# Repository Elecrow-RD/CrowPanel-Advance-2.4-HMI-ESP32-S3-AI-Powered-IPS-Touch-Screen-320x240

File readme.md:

## Menu
### 1, Product picture
### 2, Product version number
### 3, product information
### 4, Use the driver module
### 5,Quick Start
### 6,Folder structure.
### 7,Pin definition
### 8,Guidelines for downloading some of the files from the github repository

### 1, Product picture

### 2, Product version number

|      | Hardware | Software | Remark |
| ---- | -------- | -------- | ------ |
| 1    | V1.0     | V1.0     | old |
| 1    | V1.1     | V1.1     | old |
| 1    | V1.2     | V1.2     | latest |

### Version update points:

**Version 1.1** 

V1.1 upgraded, optimized the amplifier circuit, better sound quality, and use IO21 to control mute. i2s_mic changed to two pins IO9 and IO10 control.

**Version 1.2** 

Only the button component has been updated. All other hardware and I/O pins remain the same as in the previous version.

### 3, product information

| Main Chip-**ESP32-S3-WROOM-1-N16R8**         |                                                              |
| -------------------------------------------- | ------------------------------------------------------------ |
| CPU/SoC                                      | high-performance Xtensa 32-bit LX7 dual-core processor, with a  up to 240MHz |
| System Memory                                | 512KB SRAM、8M PSRAM                                         |
| Memory                                       | 16M Flash，384KB ROM                                         |
| Development Language                         | MicroPython、C/C++                                           |
| Development Environment                      | ESP-IDF、Arduino IDE、LVGL、PlatformIO、MicroPython         |
| **Screen**                                   |                                                              |
| Size                                         | 2.4 inch                                                     |
| Diver IC                                     | ST7789                                                       |
| Resolution                                   | 800*480                                                      |
| Display Panel                                | IPS Panel                                                    |
| Touch Panel                                  | Capacitive Single Touch                                      |
| Viewing Angle                                | 178°                                                         |
| Brightness                                   | 400 cd/m²(Typ.)                                              |
| Color Depth                                  | 16-bit                                                       |
| **Wireless Communication - Onboard Antenna** |                                                              |
| WiFi                                         | Support 2.4GHz, 802.11a/b/g/n                                |
| Bluetooth                                    | Support Bluetooth 5.0 and BLE                                |
| Other                                        | **Zigbee、nRF2401、Matter、Thread and Wi-Fi 6 (Optional)**   |
| **Interface/Function**                       |                                                              |
| Interface                                    | USB port, UART, I2C, SD card slot, battery socket, speaker port, microphone, etc. |
| Function                                     | Audio amplifier, volume control, battery charge management, USB to UART, etc. |
| **Button/LED Indicator**                     |                                                              |
| Reset Button                                 | Yes, press to reset device                                   |
| Boot Button                                  | Yes, press and hold the power button to burn the program     |
| PWR                                          | Power indicator                                              |
| CHG                                          | Lithium battery charging status, completion indication       |
| **Other**                                    |                                                              |
| Installation method                          | Back hanging, fixed hole                                     |
| Operating temperature                        | -20~70 °C                                                    |
| Storage temperature                          | -30~80 °C                                                    |
| Power Input                                  | 5V/2A, USB or UART terminal                                  |
| Dimensions                                   | 77.1*51.8*15.8*mm                                            |

### 4, Use the driver module

| Name   | dependency library                      |
| ------ | --------------------------------------- |
| LVGL   | lvgl/lvgl@8.3.3                         |
| ST7789 | Adafruit GFX Library<br/>version=1.11.0 |

### 5,Quick Start

### Arduino IDE starts

#### Teaching Case Path：./example/example_code2.4

1.Download the library files used by this product to the 'libraries' folder.

C:\Users\Documents\Arduino\libraries\

2.Open the Arduino IDE

3.Open the code configuration environment and burn it

### ESP-IDF starts

#### Teaching Case Path：./example/idf_code

1.Right-click on an empty space in the project folder and select "Open with VS Code" to open the project.

2.In the IDF plug-in, select the port, then compile and flash

### 6,Folder structure.

|--3D file： Contains 3D model files (.stp) for the hardware. These files can be used for visualization, enclosure design, or integration into CAD software.

|--Datasheet: Includes datasheets for components used in the project, providing detailed specifications, electrical characteristics, and pin configurations.

|--Eagle_SCH&PCB: Contains **Eagle CAD** schematic (`.sch`) and PCB layout (`.brd`) files. These are used for circuit design and PCB manufacturing.

|--example: Provides example code and projects to demonstrate how to use the hardware and libraries. These examples help users get started quickly.

|--factory_firmware: Stores pre-compiled factory firmware that can be directly flashed onto the device. This ensures the device runs the default functionality.

|--factory_sourcecode:  Contains the source code for the factory firmware, allowing users to modify and rebuild the firmware as needed.

|--libraries: Includes necessary libraries required for compiling and running the project. These libraries provide drivers and additional functionalities for the hardware.

|--Squareline_studio Instructions for use: Squareline_studio instructions: Demonstrate the use of squareline studio.

### 7,Pin definition

#define SD_MOSI 6
#define SD_MISO 4
#define SD_SCK 5
#define SD_CS 7 

cfg.pin_sclk = 42;  // SPI、SCLK

cfg.pin_mosi = 39;  // SPI、CLK

cfg.pin_miso = -1;  // SPI、MISO

cfg.pin_dc = 41; 

#define TOUCH_GT911_SCL 16

#define TOUCH_GT911_SDA 15

### 8,Guidelines for downloading some of the files from the github repository

##### 1, open the link in your browser: https://downgit.github.io/

##### 2, paste the URL of the GitHub destination folder in the input box (example format: `https://github.com/username/repository name/tree/branch name/folder path`)

##### 3, even a that way to download the file.

①Click the “Create Download Link” button to create a download link, copy the link and open it with your browser to download the contents of the corresponding folder directly.

②Click Download, and you can also download it directly.

#### Note: DownGit downloads are stored by default in **your browser's default downloads folder**, usually:

- **Windows**: `C:\Users\your username\Downloads\` (downloads folder)
- **macOS**: `~/Downloads/` (downloads folder)
- **Linux**: `~/Downloads/` (Downloads folder)

If you change the default download path in your browser, the file will be stored in the download location you set. You can find the downloaded file path in your browser's **Download History** (shortcut `Ctrl + J` or `Cmd + J`).

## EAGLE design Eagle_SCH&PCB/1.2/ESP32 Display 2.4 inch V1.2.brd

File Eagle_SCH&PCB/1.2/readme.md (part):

# 2.4-Inch ESP32-S3 Display Product Hardware Driver Guide

| Item | Details |
|---|---|
| Document Version | V1.0 |
| Applicable Hardware | ESP32 Display 2.4 inch V1.2 |
| Preparation Date | 2026-07-30 |
| Author | OpenAI Codex (cross-validated against project materials) |
| Document Status | Baseline version suitable for maintenance, porting, and handoff |

## 1. Document Purpose and Determination Rules

This document cross-validates the onboard and supported peripherals based on the mainboard Eagle schematic/PCB, schematic PDF, and verified Arduino examples in the project. Its purpose is not to repeat component datasheets, but to specify the pins, buses, initialization sequence, software dependencies, and resource conflicts actually used by this product.

The evidence priority is as follows:

1. Actual execution paths and parameters in verified examples;
2. Net connections in `1.2/ESP32 Display 2.4 inch V1.2.sch`;
3. `.brd`, PDF, code comments, and unexecuted candidate configurations;
4. Conventional component usage is used only as supporting information and does not override the configuration verified in this project.

If the code and schematic are inconsistent, this document follows the verified code as required and records the differences in Chapter 6. Components that exist in third-party libraries but are neither connected to this board nor called by the examples are not considered peripherals of this product.

## 2. Reference Baseline

| Type | Path | Purpose |
|---|---|---|
| Mainboard schematic source file | `1.2/ESP32 Display 2.4 inch V1.2.sch` | Primary evidence for components, net names, and electrical connections |
| PCB source file | `1.2/ESP32 Display 2.4 inch V1.2.brd` | Verification of assembled components, NC status, and layout |
| Mainboard schematic PDF | `1.2/ESP32-Display-2.4-inch-V1.2.pdf` | Manual graphical verification |
| LCD/LVGL/touch | `2.4_2.8_Arduino/lesson-03/2.4_2.8_LVGL/` | Verified configuration for LCD, backlight, GT911, and LVGL |
| Backlight PWM | `2.4_2.8_Arduino/lesson-03/pwn version/pwm/pwm.ino` | LEDC PWM parameters |
| SD card | `2.4_2.8_Arduino/lesson-04/SD_CrowPanel_ESP32_Advance_HMI_2.4_2.8/` | Verified SPI SD configuration |
| Audio output | `2.4_2.8_Arduino/lesson-02/OnlineAudio_small/OnlineAudio_small.ino` | I2S amplifier driver configuration |
| nRF24 | `2.4_2.8_Arduino/lesson-06/READ/`, `WRITE/` | External nRF24L01 transceiver configuration |
| LoRaWAN | `2.4_2.8_Arduino/lesson-07/code/sendATcommands_2.4_2_8/` | External SX1262 and RadioLib parameters |
| Zigbee/UART | `2.4_2.8_Arduino/lesson-08/zigbee_2.4_2_8/` | External wireless module UART configuration |
| Zigbee module schematic | `2.4_2.8_Arduino/lesson-08/Wireless_Module_ESP32-H2_V1.1_Schematic.pdf` | Reference for the supported external module; not an onboard mainboard component |

Note: The repository does not contain Git metadata, so commit history cannot be used to establish the historical “verified” version. This document treats the current tutorial example code as the user-specified verified baseline.

## 3. Peripheral Overview

| Category | Peripheral/Component | Onboard | Primary Interface | Key Pins | Software Status |
|---|---|---:|---|---|---|
| MCU | ESP32-S3-WROOM-1 | Yes | GPIO Matrix | See Chapter 4 | Arduino-ESP32 |
| Display | 2.4-inch 320×240 TFT, handled as ST7789 in code | Yes | SPI2, Mode 0 | SCK42/MOSI39/DC41/CS40 | LovyanGFX verified |
| Touch | Capacitive touch, handled as GT911 in code | On display FPC | I2C0 | SDA15/SCL16; verified reset sequence uses 1/2 | TAMC_GT911/LovyanGFX paths coexist |
| Backlight | TFT LED + transistor | Yes | GPIO/PWM | GPIO38 | Digital switching and LEDC verified |
| Storage | MicroSD | Yes | SPI/HSPI | MISO4/SCK5/MOSI6/CS7 | Arduino SD/FS verified |
| Audio output | NS4168 digital amplifier + speaker connector | Yes | I2S | BCLK13/LRCLK11/DATA12/CTRL21 | ESP32-audioI2S verified |
| Audio input | PDM microphone | Yes | PDM | CLK9/DATA10 | Confirmed by schematic; no capture example found |
| Alert device | Active/passive buzzer B1 | Yes | GPIO | GPIO8, through NPN | Confirmed by schematic; no example found |
| USB debugging | CH340K + USB-C J3 | Yes | UART0/USB | ESP TXD0/RXD0, through level shifting | Automatic download circuitry implemented |
| Native USB | USB-C J4 | Yes | USB 2.0 | GPIO19 D- / GPIO20 D+ | Arduino USB CDC/JTAG available; no dedicated project example |
| Expansion UART | HY2.0 J6 | Yes | UART1 | TX17/RX18 | Confirmed by schematic |
| Expansion I2C | HY2.0 J7 | Yes | I2C | SDA15/SCL16 | Shares the bus with touch |
| Wireless expansion SPI | J8/J9 | Yes | SPI + control | MISO9/MOSI3/SCK10; control pins vary by module | nRF24/SX1262 verified |
| nRF24L01 | External module | No | SPI | CE1/CSN2/MISO9/MOSI3/SCK10 | RF24 verified |
| SX1262 LoRa | External module | No | SPI | NSS0/DIO1=1/NRST2/BUSY46 | RadioLib verified |
| Zigbee/ESP32-H2 | External module | No | UART1 | ESP RX2/TX1 | Serial reception verified |
| Wi-Fi/BLE | Integrated into ESP32-S3 | Yes | On-chip radio | No external GPIO | Wi-Fi audio example verified |
| Battery charging | TP4059 + battery connector J10 | Yes | Analog power | CHRG/DONE monitored by STC8 | Autonomous hardware operation |
| Boost/system power | RY3420, AO3401, Schottky OR | Yes | Analog power | No ESP initialization | Autonomous hardware operation |
| Power/bus switches | SGM3799, MOSFET switches | Yes | GPIO control | GPIO45, 9, 10, 14, 21 | Partially controlled by examples |
| Battery/charging indicator | STC8G1K08A + bi-color LED | Yes | Independent MCU | CHRG/DONE/TXD/RXD | Firmware not included in this repository |
| Buttons | RESET K2, BOOT K1 | Yes | Active-low | EN, GPIO0 | Hardware boot/download |

## 4. Unified GPIO Resource Table

| GPIO | Schematic Net/Connection | Verified Use | Electrical/Multiplexing Notes |
|---:|---|---|---|
| 0 | `IO0_W_CS`, BOOT button, J8 | SX1262 NSS | Boot strapping pin; peripherals must not hold it low during power-up/reset |
| 1 | `IO1_ESP_TXD2`, J9 | nRF24 CE; SX1262 DIO1; Zigbee TX; temporarily used by the verified GT911 reset sequence | Severe multi-scenario conflict; cannot be used concurrently |
| 2 | `IO2_ESP_RXD2`, J8 | nRF24 CSN; SX1262 NRST; Zigbee RX; temporarily used by the verified GT911 reset sequence | Severe multi-scenario conflict; cannot be used concurrently |
| 3 | `IO3_W_MOSI`, J9 | Wireless expansion MOSI | SPI push-pull output |
| 4 | `IO4_SD_MISO` | MicroSD MISO | SPI input; card socket includes pull-up |
| 5 | `IO5_SD_SCK` | MicroSD SCK | SPI clock output |
| 6 | `IO6_SD_MOSI` | MicroSD MOSI | SPI push-pull output |
| 7 | `IO7_SD_CS` | MicroSD CS | Active-low; keep high when idle |
| 8 | `IO8_BEEP` | Buzzer | Drives an NPN through 1 kΩ; should default low |
| 9 | SGM3799 COM2 | Wireless MISO or PDM MIC CLK | Physical path selected by GPIO45; direction changes by scenario |
| 10 | SGM3799 COM3 | Wireless SCK or PDM MIC DATA | Physical path selected by GPIO45; direction changes by scenario |
| 11 | `IO11_I2S_LRCLK` | Amplifier LRCLK | I2S output |
| 12 | `IO12_I2S_SDIN` | Amplifier serial audio data | I2S output; net name is assigned from the amplifier’s perspective |
| 13 | `IO13_I2S_BCLK` | Amplifier BCLK | I2S output |
| 14 | `IO14_TFT_PWR` | TFT/touch power control circuit | Current display examples do not configure it actively; verify the assembly revision before making changes |
| 15 | `IO15_SDA` | Touch and J7 SDA | I2C open-drain; schematic shows 4.7 kΩ pull-up to 3.3 V |
| 16 | `IO16_SCL` | Touch and J7 SCL | I2C open-drain; schematic shows 4.7 kΩ pull-up to 3.3 V |
| 17 | `ESP_TXD1` | J6 UART TX | 3.3 V CMOS |
| 18 | `ESP_RXD1` | J6 UART RX | 3.3 V CMOS; the LVGL example only configures it as an unused output, and this ineffective configuration should be removed |
| 19 | `ESP_D-` | Native USB D- | Do not use as a general-purpose GPIO |
| 20 | `ESP_D+` | Native USB D+ | Do not use as a general-purpose GPIO |
| 21 | `IO21_NS_CTRL` | NS4168 control | Example drives it low to enable audio; polarity follows the code |
| 38 | `IO38_LED_BK` | Backlight enable/PWM | Active-high; driven through a transistor and does not carry LED current directly |
| 39 | `IO39_TFT_SDA` | LCD MOSI | Write-only path; code sets MISO=-1 |
| 40 | `IO40_TFT_CS` | LCD CS | Active-low |
| 41 | `IO41_TFT_RS` | LCD D/C | Command/data selection |
| 42 | `IO42_TFT_SCK` | LCD SCK | Highest verified configuration is 80 MHz |
| 45 | `IO45_SPISW_ITCHING` | SGM3799 bus selection | Wireless examples drive it low; boot strapping pin, so external voltage must be handled carefully during reset |
| 46 | `IO46_BOOT_BUSY` | SX1262 BUSY, J8 | ESP32-S3 input-only/strapping-related pin; suitable for BUSY input and must not be used as a general-purpose output |
| 47 | `IO47_TP_INT` | Touch INT in schematic | Current GT911 `touch.h` path configures it as -1 and uses polling; LovyanGFX candidate configuration specifies 47 |
| 48 | `IO48_TP_RST` | Touch RST in schematic | Not used by the currently verified code; major discrepancy exists |

## 5. Detailed Driver Instructions for Each Peripheral

### 5.1 ESP32-S3-WROOM-1 MCU

- Power: The module’s `3V3` is connected to `ESP_3V3` through FB1; EN is controlled by a 10 kΩ pull-up, a 1 µF RC circuit, and the RESET button.
- Boot: The BOOT button pulls GPIO0 low; the RESET button pulls EN low. For downloading, keep GPIO0 low before resetting.
- Software layer: Arduino-ESP32, with ESP-IDF HAL/drivers underneath. The graphics example does not explicitly create RTOS tasks, but the Arduino core runs FreeRTOS internally.
- Memory: The LVGL example allocates two 320×240 RGB565 full-screen buffers in PSRAM. Each buffer is 153,600 bytes, for a total of approximately 300 KiB. PSRAM must be enabled for the target module/in the Arduino menu.
- Serial logging: All examples use `Serial.begin(115200)`.

### 5.2 ST7789 TFT LCD

**Connections and Protocol**

| Signal | GPIO | Configuration |
|---|---:|---|
| SCK | 42 | SPI2_HOST clock, push-pull |
| MOSI/SDA | 39 | Unidirectional write data, push-pull |
| D/C/RS | 41 | GPIO output |
| CS | 40 | GPIO/SPI chip select, active-low |
| RST | No software GPIO | `pin_rst=-1`; handled by the RC/power network in the schematic |
| BL | 38 | Active-high or PWM |

Key configuration: SPI Mode 0, 80 MHz write frequency, 16 MHz read-frequency field, but `MISO=-1` and `readable=false`; automatic DMA channel; panel memory size of 240×320; logical display resolution of 320×240; `invert=true`, `rgb_order=false`, and `offset_rotation=3`.

Software dependencies: LovyanGFX `lgfx::Panel_ST7789` + `lgfx::Bus_SPI`. The UI example additionally uses LVGL with RGB565, dual full-screen PSRAM buffers, and full-refresh mode, with `lv_timer_handler()` called approximately every 5 ms.

Key configuration example:

```cpp
cfg.spi_host = SPI2_HOST;
cfg.spi_mode = 0;
cfg.freq_write = 80000000;
cfg.pin_sclk = 42; cfg.pin_mosi = 39; cfg.pin_dc = 41;
panel.pin_cs = 40; panel.pin_rst = -1;
```

Initialization sequence: Call `gfx.init()` first. If DMA is required, then call `gfx.initDMA()` and `gfx.startWrite()`. Finally, drive GPIO38 high to turn on the backlight. When a white or black screen occurs, first distinguish between “LCD not initialized” and “backlight not enabled.”

### 5.3 Capacitive Touch (Handled as GT911 in the Actual Code)

- Bus: I2C0, SDA=15, SCL=16; 3.3 V open-drain bus with a 4.7 kΩ pull-up on each line on the mainboard.
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
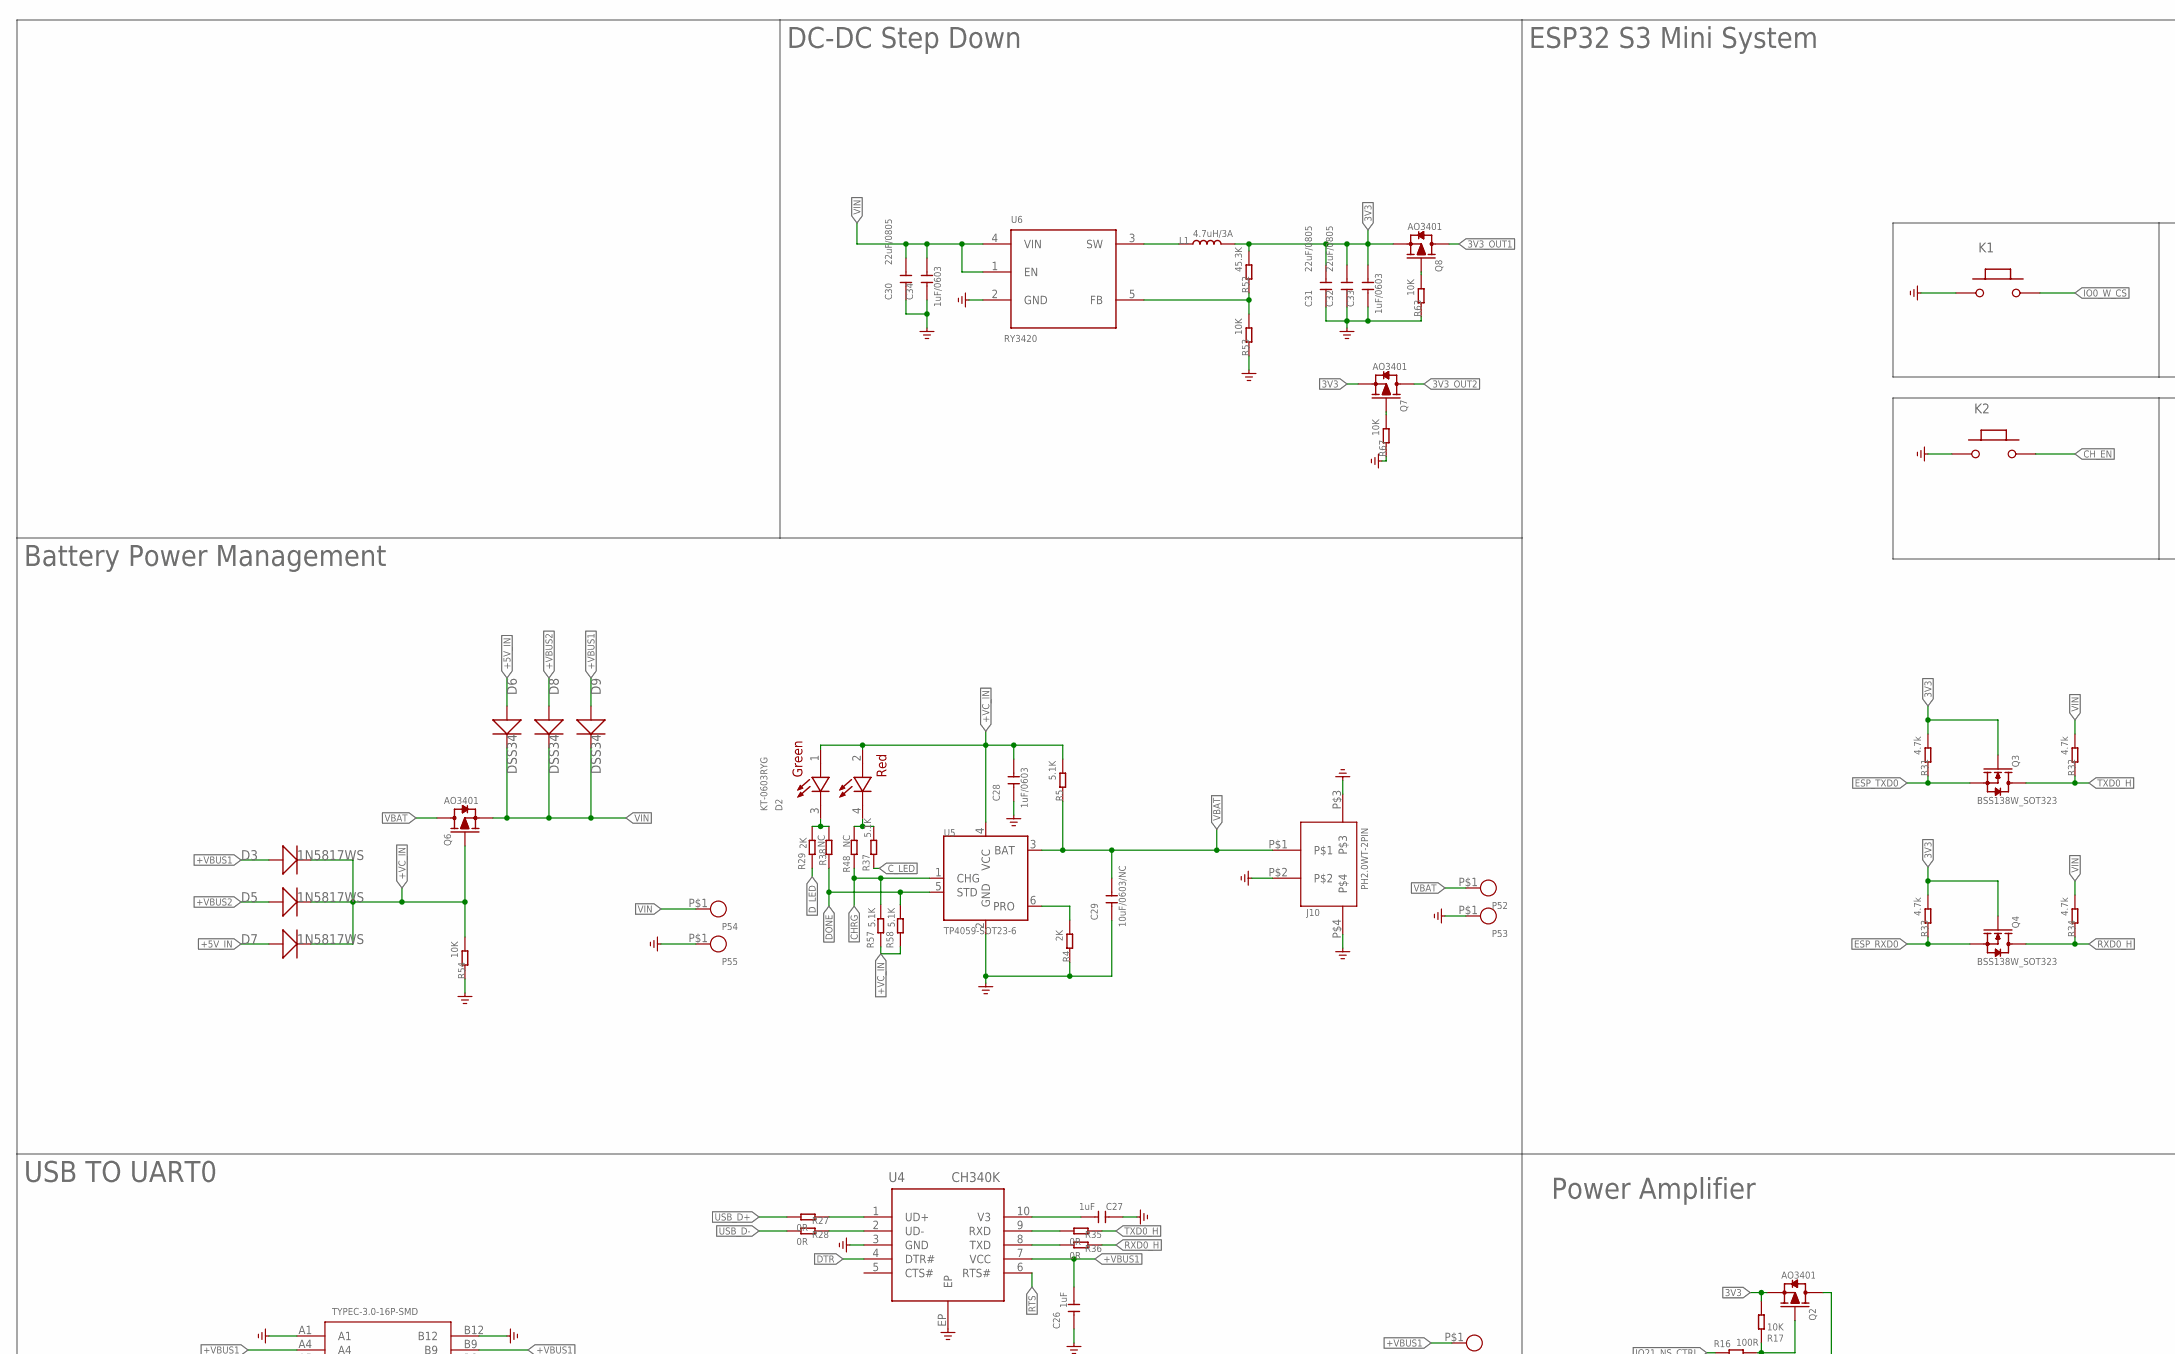
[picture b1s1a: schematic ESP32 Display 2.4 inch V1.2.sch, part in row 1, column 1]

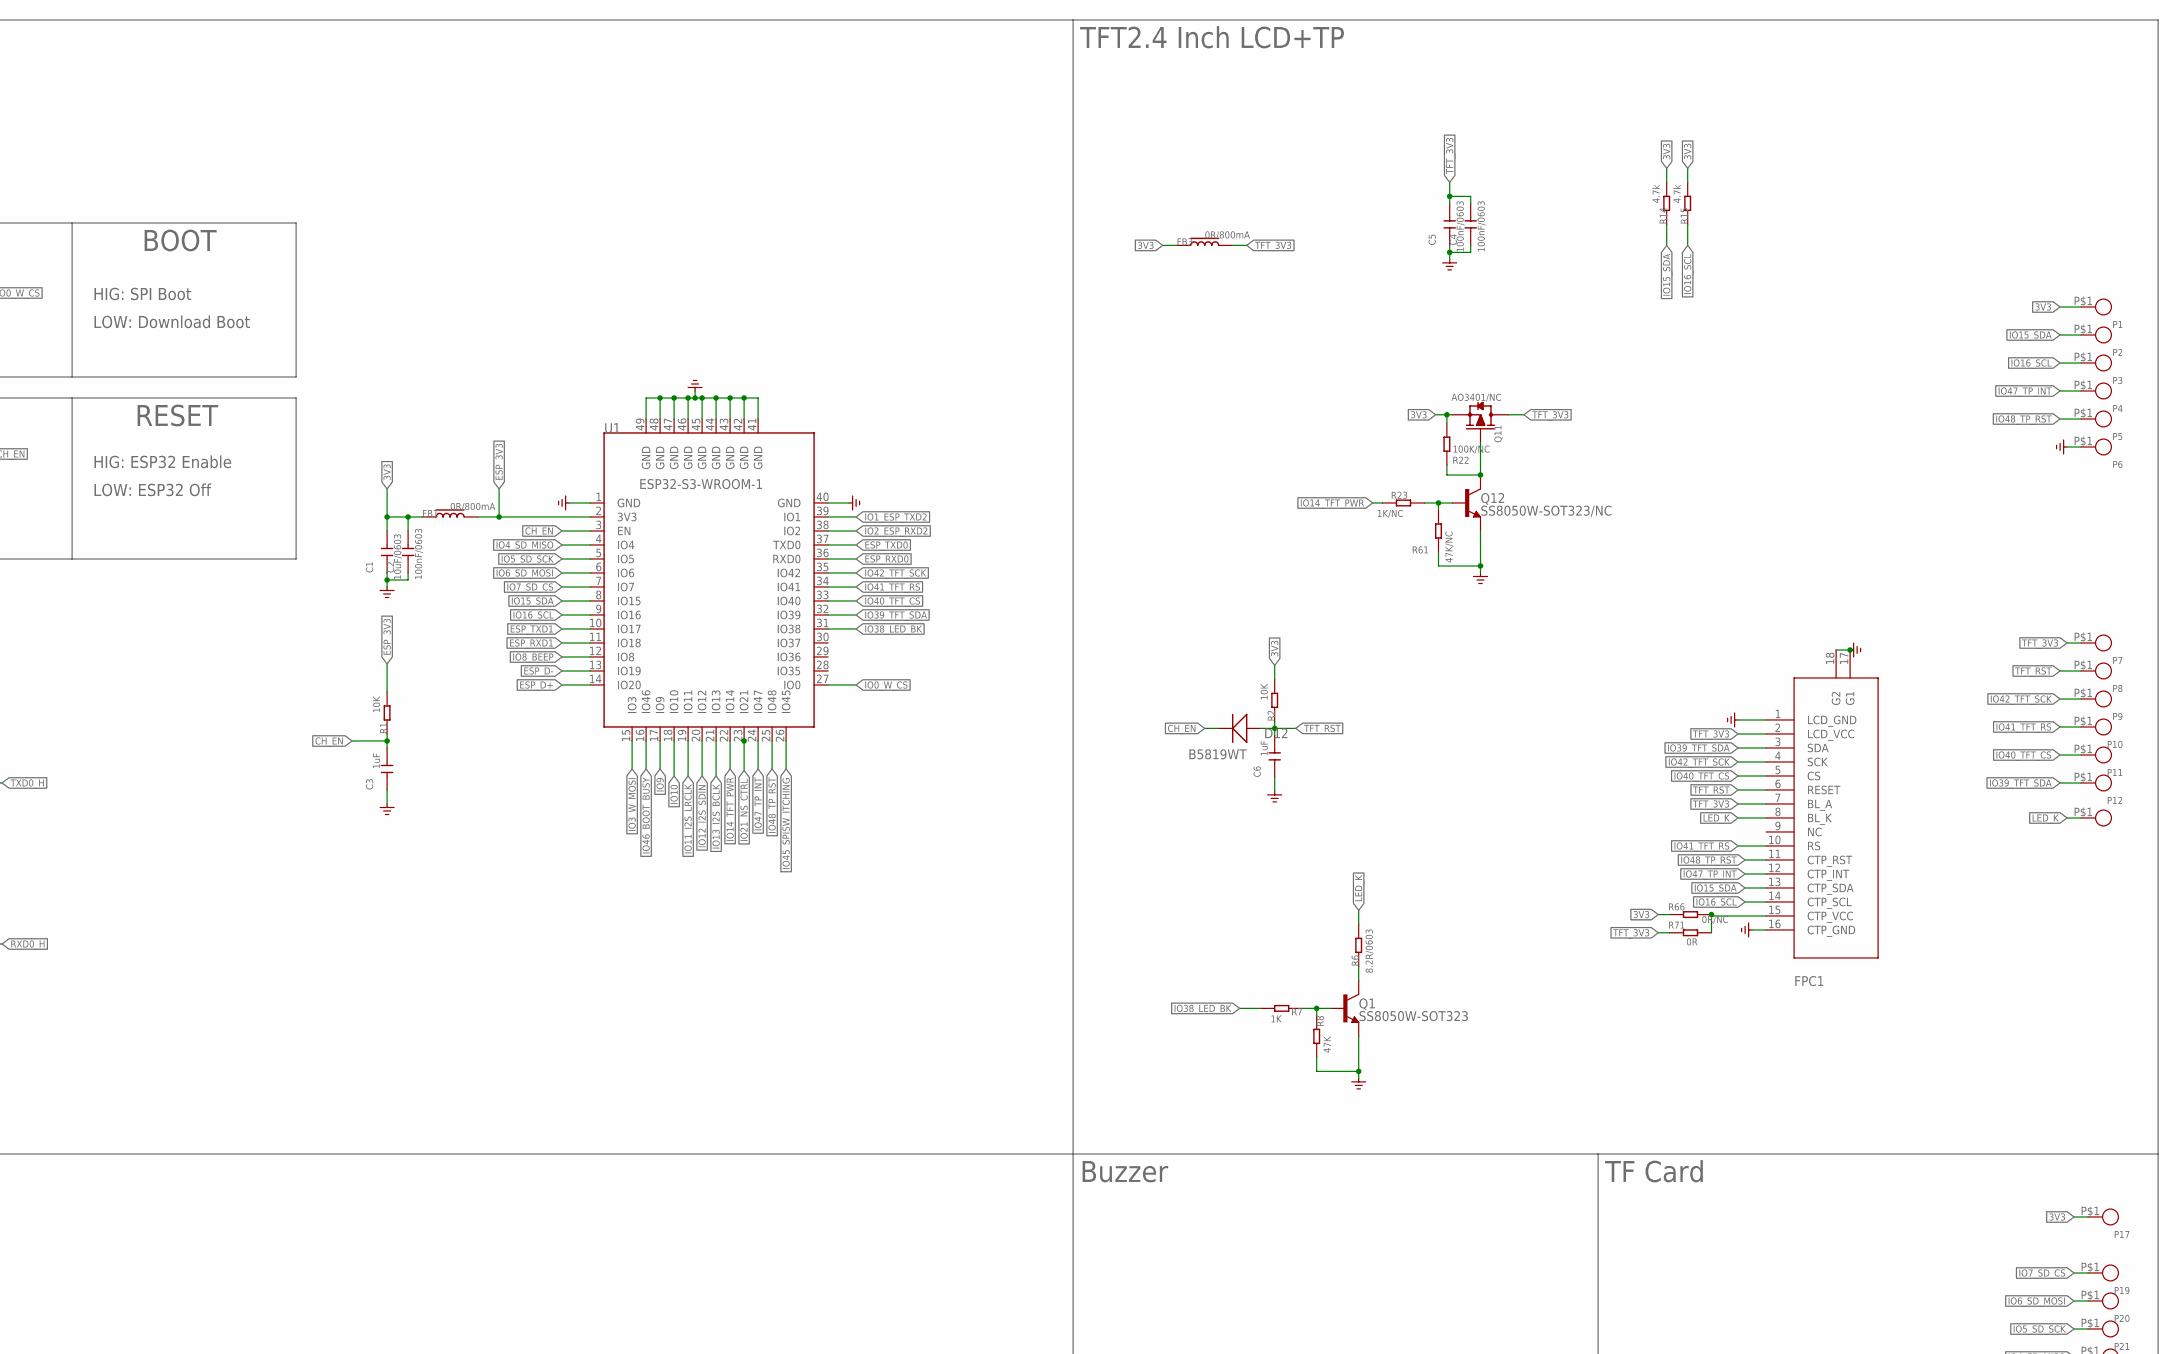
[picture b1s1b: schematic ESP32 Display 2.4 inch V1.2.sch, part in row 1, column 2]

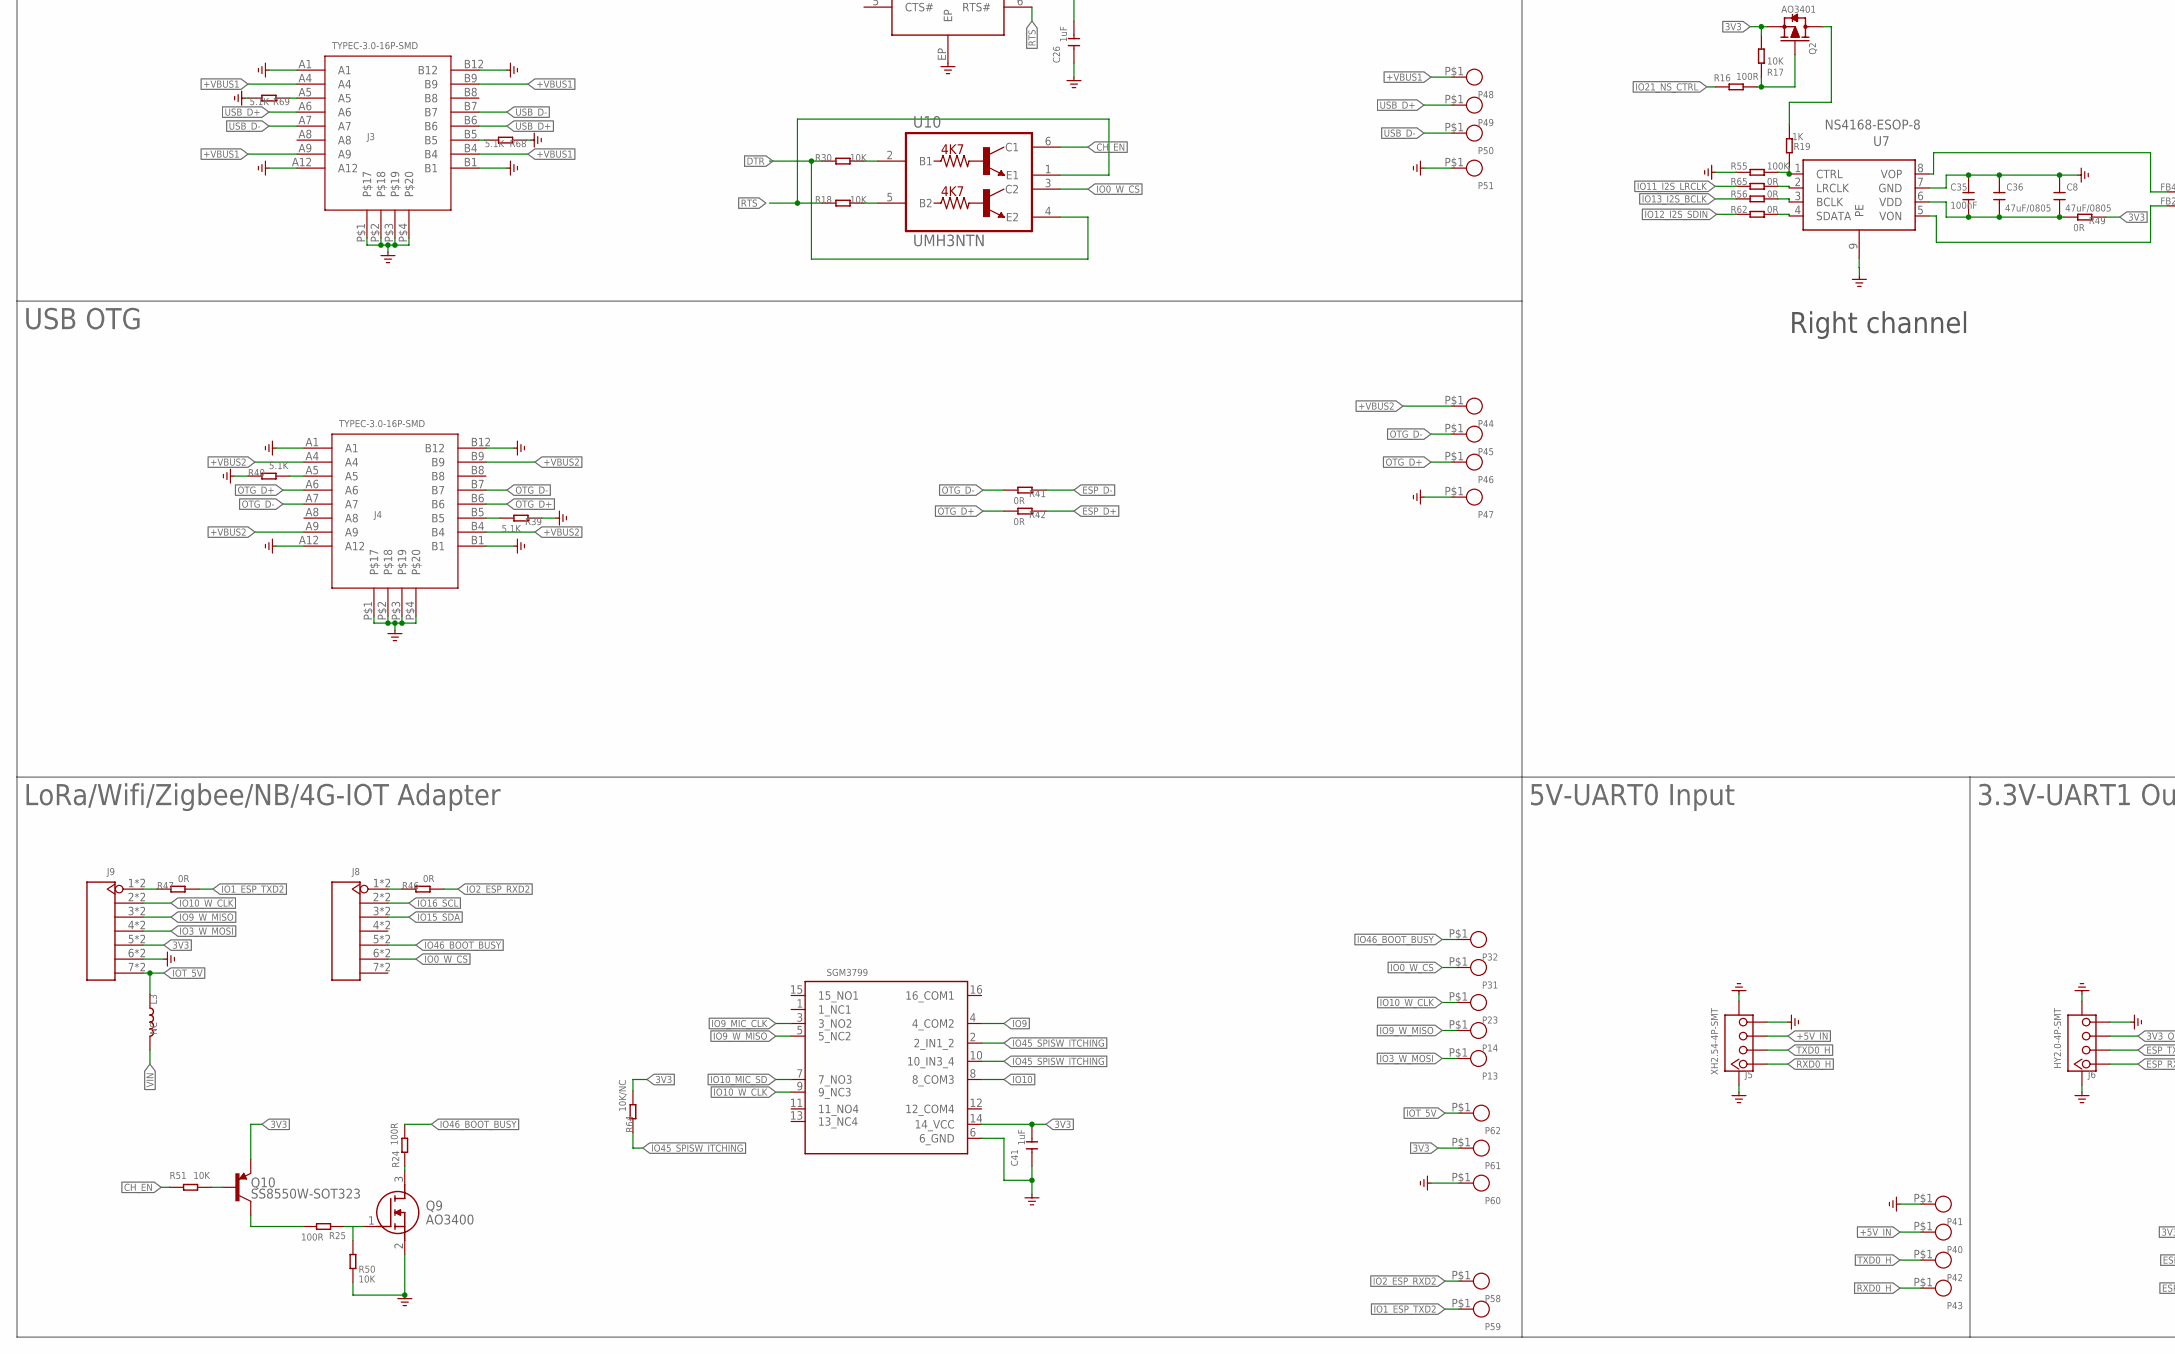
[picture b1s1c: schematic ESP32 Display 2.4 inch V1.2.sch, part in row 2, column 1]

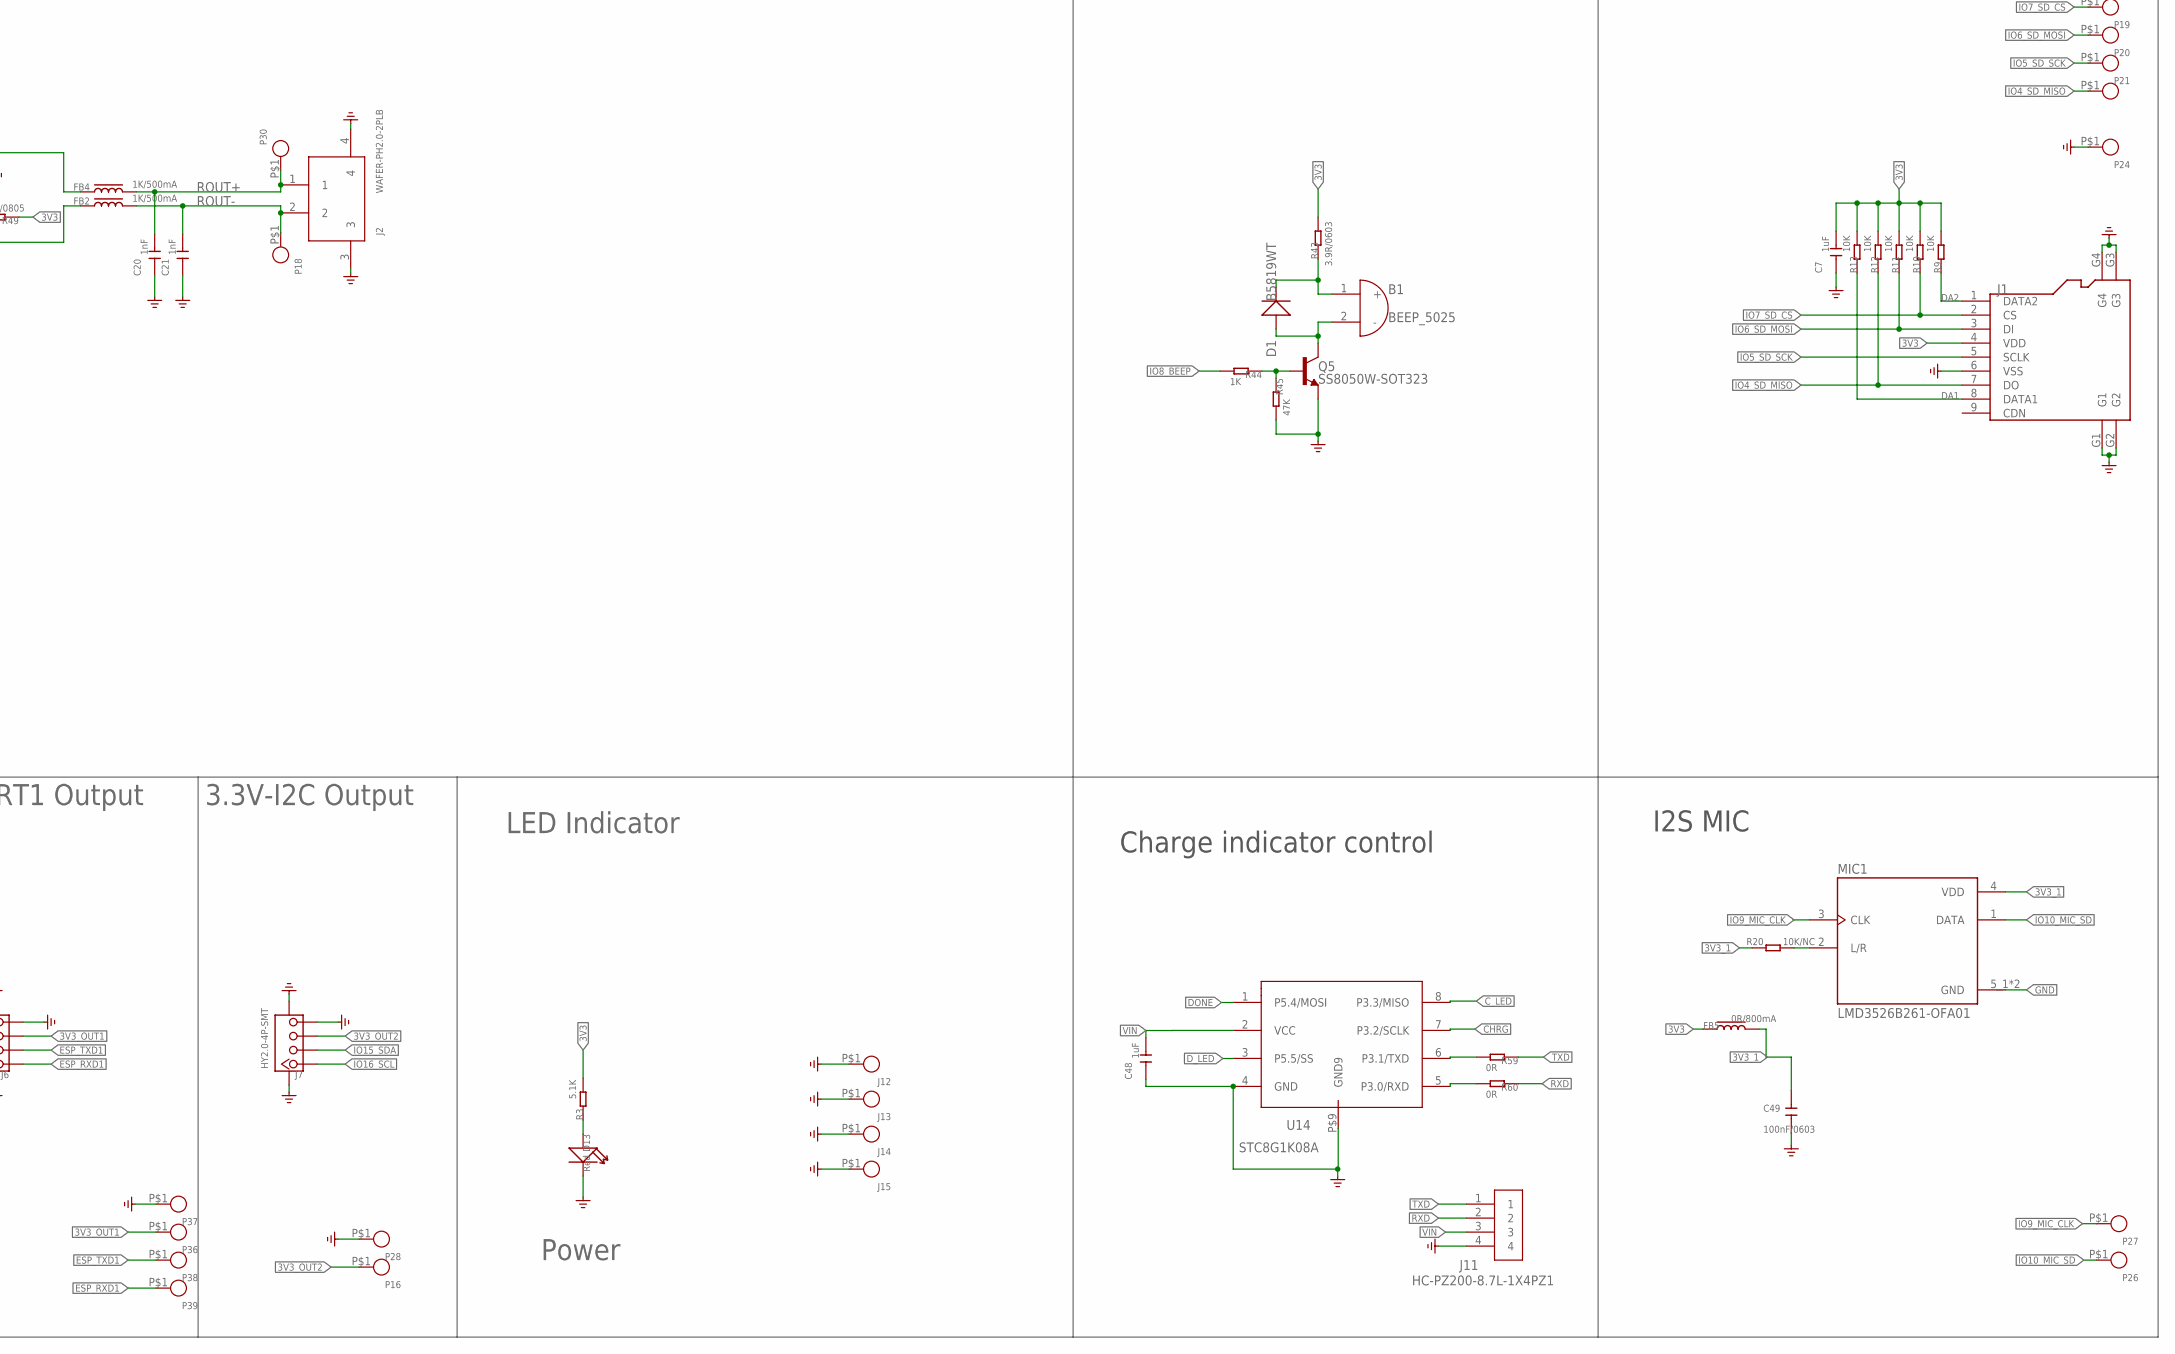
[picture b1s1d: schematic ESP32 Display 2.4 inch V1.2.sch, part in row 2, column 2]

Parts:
B1: BEEP_5025
C1: 10uF/0603; C0603
C2, C4, C5, C49: 100nF/0603; C0603
C3, C6, C7, C26, C27, C41, C48: 1uF; C0402
C8, C36: 47uF/0805; C0805
C20, C21: 1nF; C0402
C28, C33, C34: 1uF/0603; C0603
C29: 10uF/0603/NC; C0603
C30, C31, C32: 22uF/0805; C0805
C35: 100nF; C0402
D1, D12: B5819WT; D_SOD523
D2: KT-0603RYG; LED_KT-0603RYG
D3, D5, D7: 1N5817WS; D_SOD323
D6, D8, D9: DSS34; D_SOD123FL
D13: Red; LED0603
FB1, FB3, FB5: 0R/800mA; L0603
FB2, FB4: 1K/500mA; L0603
FPC1: TFT-2.4-SPI-16P; FPC-0.5MM-16P-SMD
J1: HOLDER-MICROSD-9P; 9P-SMD-W/-RING
J2: WAFER-PH2.0-2PLB; CONN-TH_2P-P2.00_XUNPU_WAFER-PH2.0-2PLB
J3, J4: TYPEC-3.0-16P-SMD; USB-3.0TYPEC-SMD
J5: XH2.54-4P-SMT; XH2.54-4P-SMD
J6, J7: HY2.0-4P-SMT; CONNECTOR_4P-SMD-2.0
J8, J9: HEADER-7P-18.28X2.5; H7-2.54-18.28X2.5X5MM
J10: PH2.0WT-2PIN
J11: HC-PZ200-8.7L-1X4PZ1; TEST-PIN-4-2.0MM
J12, J13, J14, J15: THO-M3.25MM-HOLE; THO-M3.2*5MM-HOLE
K1, K2: BUTTON; 157SW
L1: 4.7uH/3A; L0420
L3: NC; L0603
MIC1: LMD3526B261-OFA01; MIC-SMD_5P-L3.5-W2.7-P1.67
P1, P2, P3, P4, P5, P6, P7, P8, P9, P10, P11, P12, P13, P14, P15, P16, P17, P18, P19, P20, P21, P22, P23, P24, P26, P27, P28, P30, P31, P32, P36, P37, P38, P39, P40, P41, P42, P43, P44, P45, P46, P47, P48, P49, P50, P51, P52, P53, P54, P55, P58, P59, P60, P61, P62: TEST_PADPAD-1.5MM; TEST_PAD-1.5MM
Q1, Q5: SS8050W-SOT323; MOS_SOT323
Q2, Q6, Q7, Q8: AO3401; PMOS_SOT23
Q3, Q4: BSS138W_SOT323; MOS_SOT323
Q9: AO3400; SOT95P280X125-3N
Q10: SS8550W-SOT323; MOS_SOT323
Q11: AO3401/NC; PMOS_SOT23
Q12: SS8050W-SOT323/NC; MOS_SOT323
R1, R2, R9, R10, R11, R12, R13, R17, R18, R30, R50, R51, R53, R54, R63, R67: 10K; R0402
R3, R5, R37, R39, R40, R57, R58, R68, R69: 5.1K; R0402
R4, R29: 2K; R0402
R6: 8.2R/0603; R0603-SP
R7, R19, R44: 1K; R0402
R8, R45: 47K; R0402
R14, R15, R31, R32, R33, R34: 4.7k; R0402
R16, R24, R25: 100R; R0402
R20, R64: 10K/NC; R0402
R22: 100K/NC; R0402
R23: 1K/NC; R0402
R27, R28, R35, R36, R41, R42, R46, R47, R49, R56, R59, R60, R62, R65, R71: 0R; R0402
R38, R48: NC; R0402
R43: 3.9R/0603; R0603-SP
R52: 45.3K; R0402
R55: 100K; R0402
R61: 47K/NC; R0402
R66: 0R/NC; R0402
U1: ESP32-S3-WROOM-1; ESP32-S3-WROOM-1-SMD41
U4: CH340K; ESOP-10-EP-150MIL
U5: TP4059-SOT23-6; SOT23-6L
U6: RY3420; IC_SOT23-5
U7: NS4168-ESOP-8
U8: SGM3799; IC_SGM3799_TQFN2.6X1.8_16L
U10: UMH3NTN; SOP65P210X100-6N
U14: STC8G1K08A; DFN8

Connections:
3V3: C1.2, C2.2, C7.2, C31.2, C32.2, C33.2, C41.2, FB1.1, FB3.1, FB5.1, J1.4 (VDD), J9.5, J9.5-5 (5), L1.2, P1.P$1, P17.P$1, P61.P$1, Q2.2 (S), Q3.1 (G), Q4.1 (G), Q7.2 (S), Q8.2 (S), Q10.2 (E), Q11.2 (S), R2.2, R3.2, R9.2, R10.2, R11.2, R12.2, R13.2, R14.2, R15.2, R17.2, R22.2, R31.2, R33.2, R43.2, R49.1, R52.2, R64.2, R66.2, U8.14 (14_VCC)
3V3_1: C49.2, FB5.2, MIC1.4 (VDD), R20.2
3V3_OUT1: J6.3, P36.P$1, Q8.3 (D)
3V3_OUT2: J7.3, P16.P$1, Q7.3 (D)
+5V_IN: D6.+, D7.+, J5.3, P40.P$1
+VBUS1: C26.2, D3.+, D9.+, J3.A4, J3.A9, J3.B4, J3.B9, P48.P$1, U4.7 (VCC)
+VBUS2: D5.+, D8.+, J4.A4, J4.A9, J4.B4, J4.B9, P44.P$1
+VC_IN: C28.2, D2.1, D2.2, D3.-, D5.-, D7.-, Q6.1 (G), R5.2, R54.2, R57.1, R58.1, U5.4 (VCC)
CHRG: R48.1, R57.2, U5.1 (CHG), U14.7 (P3.2/SCLK)
CH_EN: C3.2, D12.-, K2.2, R1.1, R51.1, U1.3 (EN), U10.6 (C1)
C_LED: R37.1, U14.8 (P3.3/MISO)
DA1: J1.8 (DATA1), R13.1
DA2: J1.1 (DATA2), R9.1
DONE: R38.1, R58.2, U5.5 (STD), U14.1 (P5.4/MOSI)
DTR: R30.2, U4.4 (DTR#), U10.4 (E2)
D_LED: R29.1, U14.3 (P5.5/SS)
ESP_3V3: FB1.2, R1.2, U1.2 (3V3)
ESP_D+: R42.1, U1.14 (IO20)
ESP_D-: R41.1, U1.13 (IO19)
ESP_RXD0: Q4.2 (S), R33.1, U1.36 (RXD0)
ESP_RXD1: J6.1, P39.P$1, U1.11 (IO18)
ESP_TXD0: Q3.2 (S), R31.1, U1.37 (TXD0)
ESP_TXD1: J6.2, P38.P$1, U1.10 (IO17)
GND: C1.1, C2.1, C3.1, C4.1, C5.1, C6.1, C7.1, C8.2, C20.1, C21.1, C26.1, C27.1, C28.1, C29.1, C30.1, C31.1, C32.1, C33.1, C34.1, C35.2, C36.2, C41.1, C48.1, C49.1, D13.-, FPC1.1 (LCD_GND), FPC1.16 (CTP_GND), FPC1.17 (G1), FPC1.18 (G2), J1.6 (VSS), J1.G1, J1.G2, J1.G3, J1.G4, J2.3, J2.4, J3.A1, J3.A12, J3.B1, J3.B12, J3.P$1, J3.P$2, J3.P$3, J3.P$4, J4.A1, J4.A12, J4.B1, J4.B12, J4.P$1, J4.P$2, J4.P$3, J4.P$4, J5.4, J5.5 (SS1), J5.6 (SS2), J6.4, J6.SS1, J6.SS2, J7.4, J7.SS1, J7.SS2, J9.6, J9.6-6 (6), J10.P$2, J10.P$3, J10.P$4, J11.4, J12.P$1, J13.P$1, J14.P$1, J15.P$1, K1.1, K2.1, MIC1.5_1 (GND), MIC1.5_2 (GND), P6.P$1, P24.P$1, P28.P$1, P37.P$1, P41.P$1, P47.P$1, P51.P$1, P53.P$1, P55.P$1, P60.P$1, Q1.2 (E), Q5.2 (E), Q9.2 (S), Q12.2 (E), R4.1, R8.2, R39.1, R40.1, R45.2, R50.2, R53.1, R54.1, R55.2, R61.2, R63.1, R67.1, R68.1, R69.2, U1.1 (GND), U1.40 (GND), U1.41 (GND), U1.42 (GND), U1.43 (GND), U1.44 (GND), U1.45 (GND), U1.46 (GND), U1.47 (GND), U1.48 (GND), U1.49 (GND), U4.3 (GND), U4.EP, U5.2 (GND), U6.2 (GND), U7.7 (GND), U7.9 (PE), U8.6 (6_GND), U14.4 (GND), U14.P$9 (GND9)
IO0_W_CS: J8.6, J8.6-6 (6), K1.2, P31.P$1, U1.27 (IO0), U10.3 (C2)
IO1_ESP_TXD2: P59.P$1, R47.2, U1.39 (IO1)
IO2_ESP_RXD2: P58.P$1, R46.2, U1.38 (IO2)
IO3_W_MOSI: J9.4, J9.4-4 (4), P13.P$1, U1.15 (IO3)
IO4_SD_MISO: J1.7 (DO), P22.P$1, R12.1, U1.4 (IO4)
IO5_SD_SCK: J1.5 (SCLK), P21.P$1, U1.5 (IO5)
IO6_SD_MOSI: J1.3 (DI), P20.P$1, R11.1, U1.6 (IO6)
IO7_SD_CS: J1.2 (CS), P19.P$1, R10.1, U1.7 (IO7)
IO8_BEEP: R44.2, U1.12 (IO8)
IO9: U1.17 (IO9), U8.4 (4_COM2)
IO9_MIC_CLK: MIC1.3 (CLK), P27.P$1, U8.3 (3_NO2)
IO9_W_MISO: J9.3, J9.3-3 (3), P14.P$1, U8.5 (5_NC2)
IO10: U1.18 (IO10), U8.8 (8_COM3)
IO10_MIC_SD: MIC1.1 (DATA), P26.P$1, U8.7 (7_NO3)
IO10_W_CLK: J9.2, J9.2-2 (2), P23.P$1, U8.9 (9_NC3)
IO11_I2S_LRCLK: R65.2, U1.19 (IO11)
IO12_I2S_SDIN: R62.2, U1.20 (IO12)
IO13_I2S_BCLK: R56.2, U1.21 (IO13)
IO14_TFT_PWR: R23.2, U1.22 (IO14)
IO15_SDA: FPC1.13 (CTP_SDA), J7.2, J8.3, J8.3-3 (3), P2.P$1, R14.1, U1.8 (IO15)
IO16_SCL: FPC1.14 (CTP_SCL), J7.1, J8.2, J8.2-2 (2), P3.P$1, R15.1, U1.9 (IO16)
IO21_NS_CTRL: R16.1, U1.23 (IO21)
IO38_LED_BK: R7.2, U1.31 (IO38)
IO39_TFT_SDA: FPC1.3 (SDA), P12.P$1, U1.32 (IO39)
IO40_TFT_CS: FPC1.5 (CS), P11.P$1, U1.33 (IO40)
IO41_TFT_RS: FPC1.10 (RS), P10.P$1, U1.34 (IO41)
IO42_TFT_SCK: FPC1.4 (SCK), P9.P$1, U1.35 (IO42)
IO45_SPISW_ITCHING: R64.1, U1.26 (IO45), U8.2 (2_IN1_2), U8.10 (10_IN3_4)
IO46_BOOT_BUSY: J8.5, J8.5-5 (5), P32.P$1, R24.2, U1.16 (IO46)
IO47_TP_INT: FPC1.12 (CTP_INT), P4.P$1, U1.24 (IO47)
IO48_TP_RST: FPC1.11 (CTP_RST), P5.P$1, U1.25 (IO48)
IOT_5V: J9.7, J9.7-7 (7), L3.1, P62.P$1
LED_K: FPC1.8 (BL_K), P15.P$1, R6.2
unnamed: Q1.3 (C), R6.1
unnamed: D13.+, R3.1
unnamed: Q1.1 (B), R7.1, R8.1
unnamed: R59.2, U14.6 (P3.1/TXD)
unnamed: R60.2, U14.5 (P3.0/RXD)
unnamed: FB4.1, U7.8 (VOP)
unnamed: FB2.1, U7.5 (VON)
unnamed: MIC1.2 (L/R), R20.1
unnamed: Q2.1 (G), R16.2, R17.1
unnamed: R4.2, U5.6 (PRO)
unnamed: FPC1.15 (CTP_VCC), R66.1, R71.1
unnamed: Q12.1 (B), R23.1, R61.1
unnamed: Q9.1 (G), R25.1, R50.1
unnamed: R27.1, U4.1 (UD+)
unnamed: R28.1, U4.2 (UD-)
unnamed: L1.1, U6.3 (SW)
unnamed: R30.1, U10.2 (B1)
unnamed: R18.1, U10.5 (B2)
unnamed: Q8.1 (G), R63.2
unnamed: C27.2, U4.10 (V3)
unnamed: Q7.1 (G), R67.2
unnamed: R35.2, U4.9 (RXD)
unnamed: R36.2, U4.8 (TXD)
unnamed: J9.1, J9.1-1 (1), R47.1
unnamed: J4.B5, R39.2
unnamed: J4.A5, R40.2
unnamed: Q5.1 (B), R44.1, R45.1
unnamed: B1.2 (-), D1.+, Q5.3 (C)
unnamed: B1.1 (+), D1.-, R43.1
unnamed: J3.B5, R68.2
unnamed: R52.1, R53.2, U6.5 (FB)
unnamed: J3.A5, R69.1
unnamed: Q10.3 (C), R25.2
unnamed: Q10.1 (B), R51.2
unnamed: Q11.1 (G), Q12.3 (C), R22.1
unnamed: J8.1, J8.1-1 (1), R46.1
unnamed: R65.1, U7.2 (LRCLK)
unnamed: D2.3, R29.2, R38.2
unnamed: D2.4, R37.2, R48.2
unnamed: R56.1, U7.3 (BCLK)
unnamed: R62.1, U7.4 (SDATA)
unnamed: C8.1, C35.1, C36.1, R49.2, U7.6 (VDD)
unnamed: Q9.3 (D), R24.1
NS_3V3: Q2.3 (D), R19.1
NS_CTRL: R19.2, R55.1, U7.1 (CTRL)
OTG_D+: J4.A6, J4.B6, P46.P$1, R42.2
OTG_D-: J4.A7, J4.B7, P45.P$1, R41.2
ROUT+: C20.2, FB4.2, J2.1, P30.P$1
ROUT-: C21.2, FB2.2, J2.2, P18.P$1
RTS: R18.2, U4.6 (RTS#), U10.1 (E1)
RXD: J11.2, R60.1
RXD0_H: J5.1, P43.P$1, Q4.3 (D), R34.1, R36.1
TFT_3V3: C4.2, C5.2, FB3.2, FPC1.2 (LCD_VCC), FPC1.7 (BL_A), P7.P$1, Q11.3 (D), R71.2
TFT_RST: C6.2, D12.+, FPC1.6 (RESET), P8.P$1, R2.1
TXD: J11.1, R59.1
TXD0_H: J5.2, P42.P$1, Q3.3 (D), R32.1, R35.1
USB_D+: J3.A6, J3.B6, P49.P$1, R27.2
USB_D-: J3.A7, J3.B7, P50.P$1, R28.2
VBAT: C29.2, J10.P$1, P52.P$1, Q6.3 (D), R5.1, U5.3 (BAT)
VIN: C30.2, C34.2, C48.2, D6.-, D8.-, D9.-, J11.3, L3.2, P54.P$1, Q6.2 (S), R32.2, R34.2, U6.1 (EN), U6.4 (VIN), U14.2 (VCC)

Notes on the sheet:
DC-DC Step Down
Battery Power Management
USB TO UART0
USB OTG
LoRa/Wifi/Zigbee/NB/4G-IOT Adapter
5V-UART0 Input
3.3V-UART1 Output
3.3V-I2C Output
Power Amplifier
ESP32 S3 Mini System
TFT2.4 Inch LCD+TP
Buzzer
TF Card
LED Indicator
BOOT
RESET
HIG: SPI Boot
LOW: Download Boot
HIG: ESP32 Enable
LOW: ESP32 Off
Power
Right channel
Charge indicator control
I2S MIC
